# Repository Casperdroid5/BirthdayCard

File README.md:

A specialized birthdaycard containing personal text and jokes for my little brother. Containing word/component jokes on the silkscreen, 2 buttons to control the card and a few modes you can cycle trough. The code tells you everything you need. Feel free to redesign the card to your likings.

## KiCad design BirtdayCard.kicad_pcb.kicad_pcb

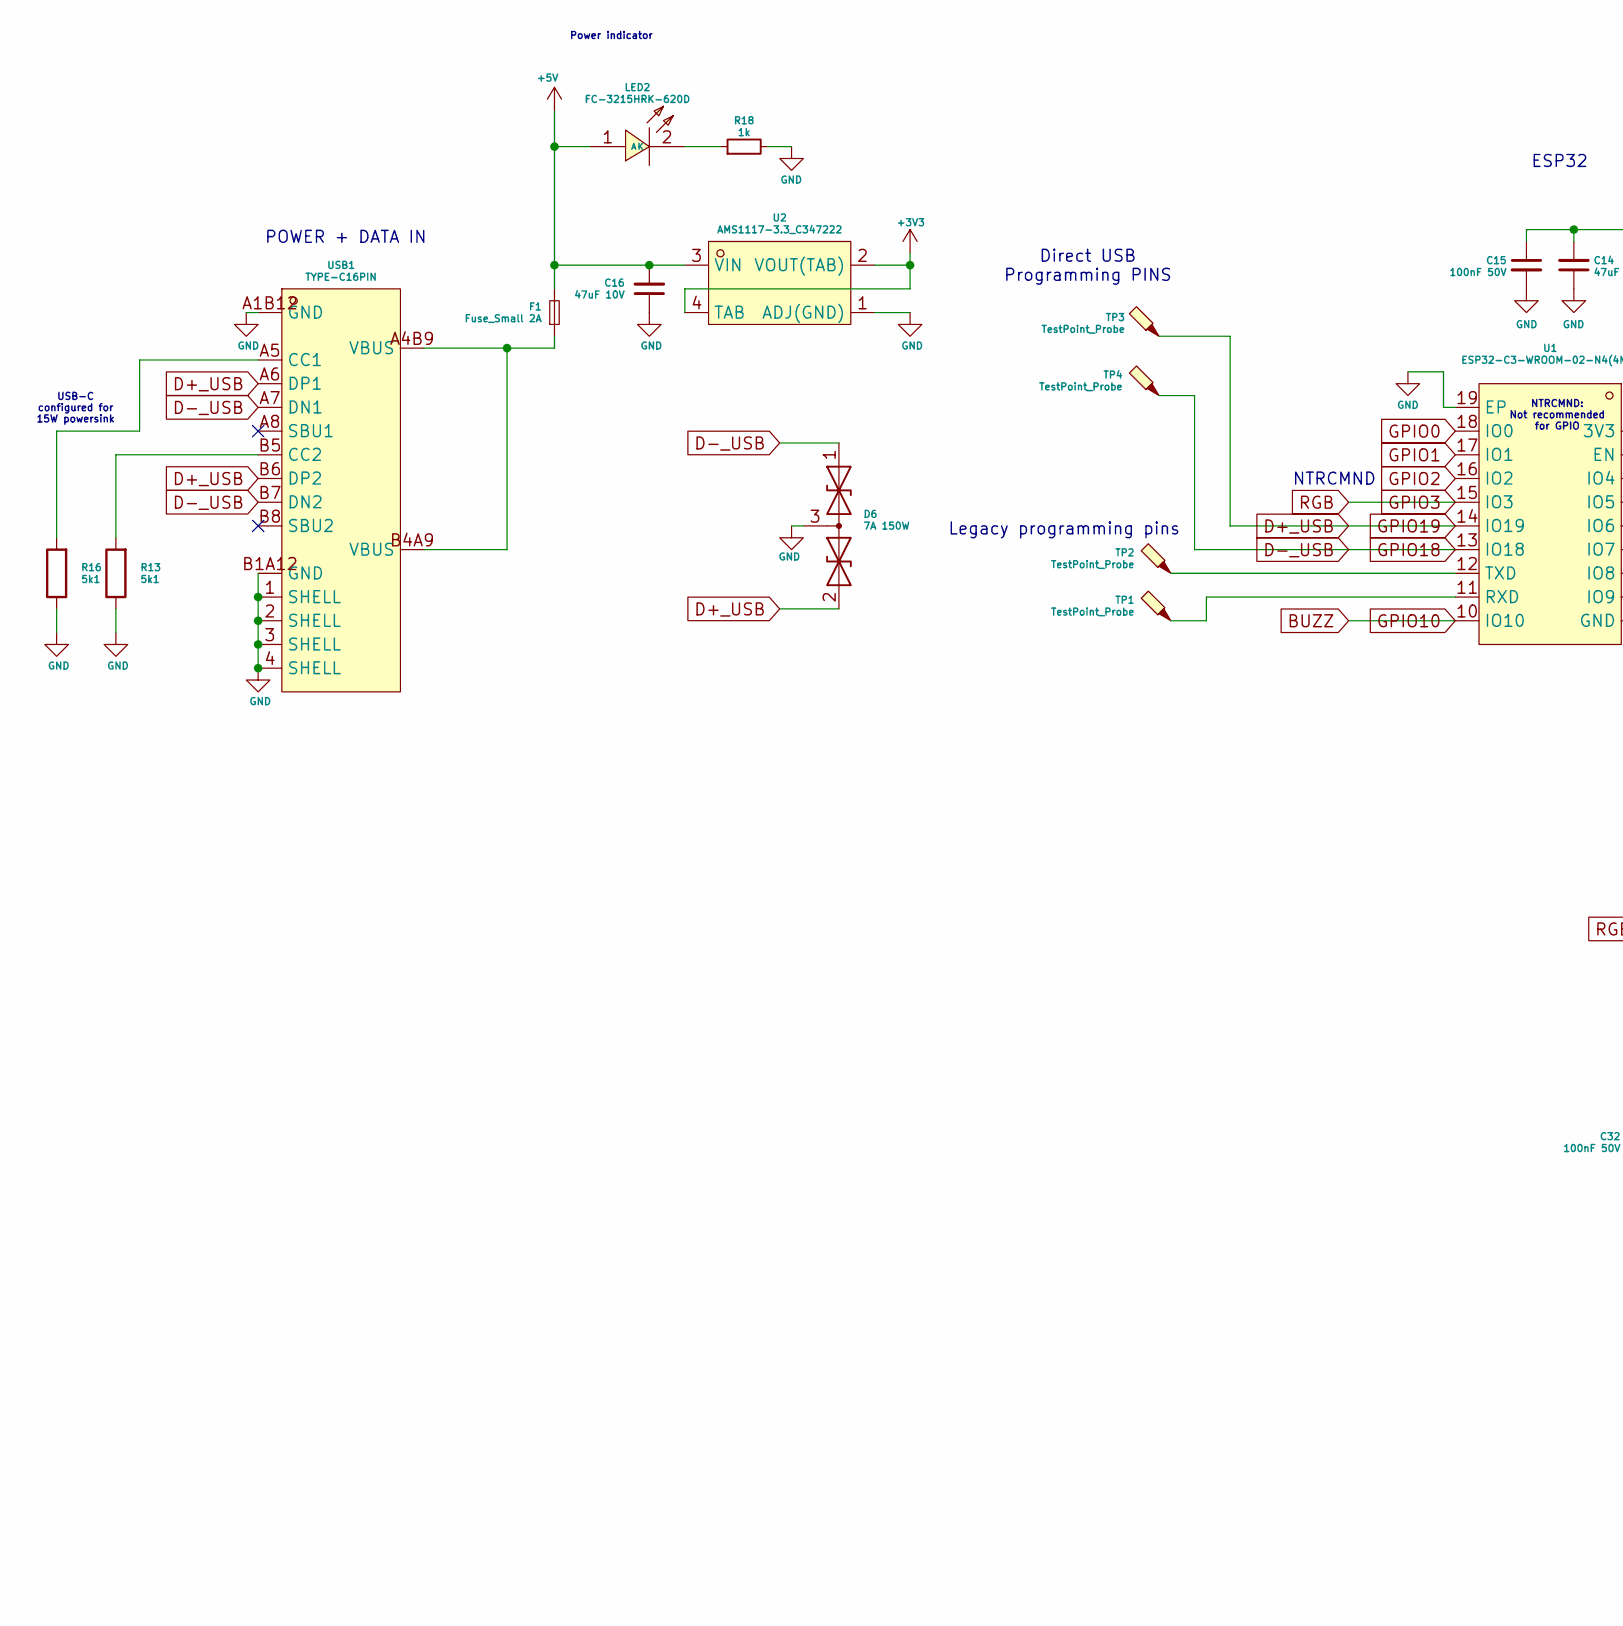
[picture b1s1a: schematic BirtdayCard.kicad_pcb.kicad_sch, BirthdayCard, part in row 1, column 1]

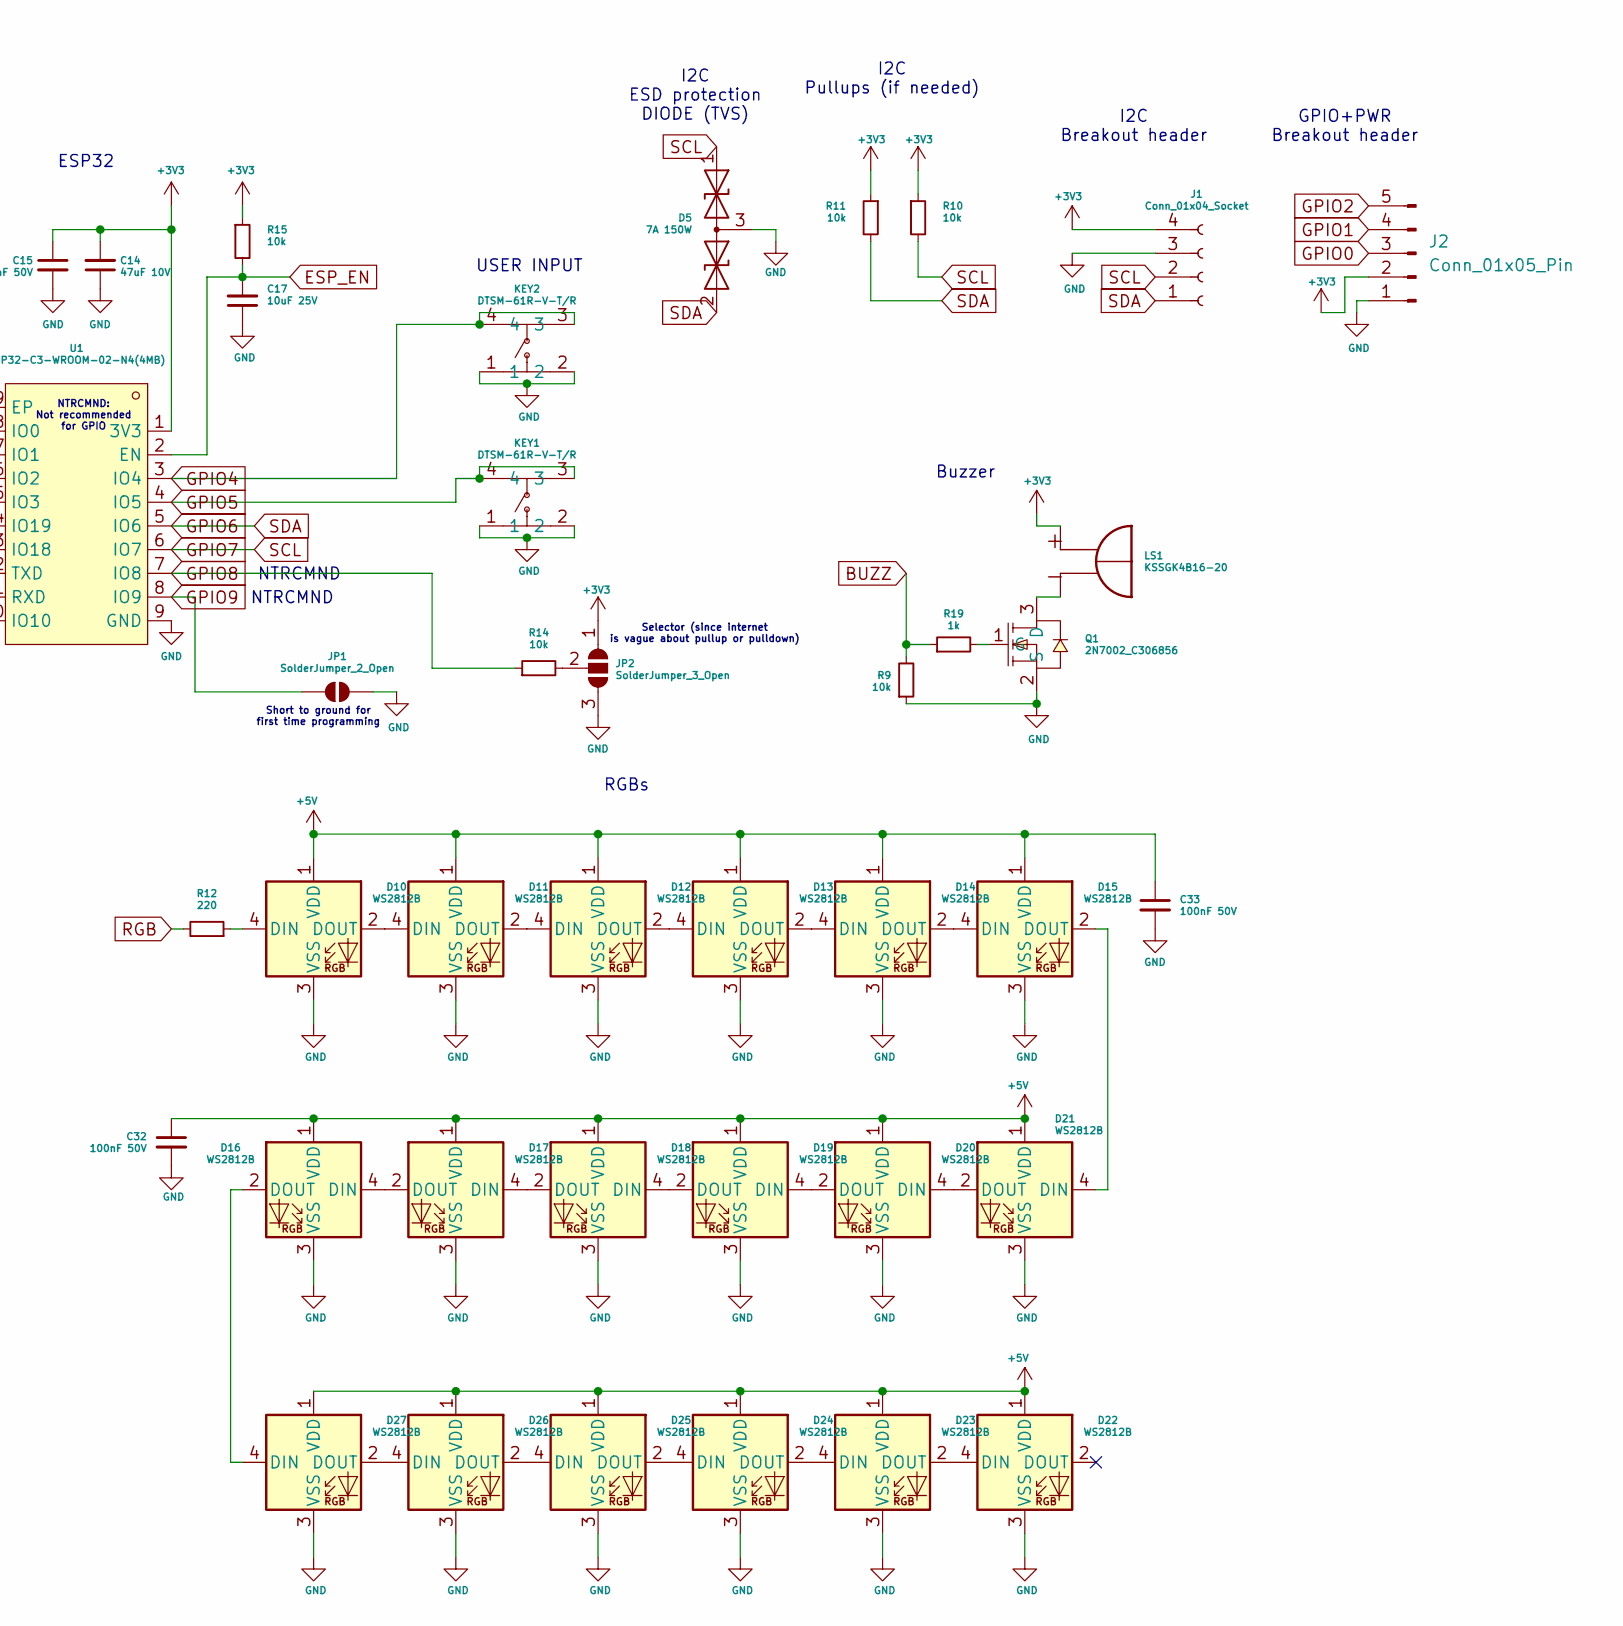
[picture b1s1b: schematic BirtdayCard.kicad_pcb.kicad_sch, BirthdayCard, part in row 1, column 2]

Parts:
C14, C16: 47uF 10V; C_1210_3225Metric_Pad1.33x2.70mm_HandSolder
C15, C32, C33: 100nF 50V; C_1210_3225Metric_Pad1.33x2.70mm_HandSolder
C17: 10uF 25V; C_1210_3225Metric_Pad1.33x2.70mm_HandSolder
D5, D6: 7A 150W; SOT-23_Handsoldering
D10, D11, D12, D13, D14, D15, D16, D17, D18, D19, D20, D21, D22, D23, D24, D25, D26, D27: WS2812B; LED-SMD_4P-L5.0-W5.0-BL_TC5050RGB
F1: Fuse_Small 2A; Fuse_1206_3216Metric_Pad1.42x1.75mm_HandSolder
J1: Conn_01x04_Socket; PinSocket_1x04_P2.54mm_Vertical
J2: Conn_01x05_Pin
JP1: SolderJumper_2_Open; SolderJumper-2_P1.3mm_Open_Pad1.0x1.5mm
JP2: SolderJumper_3_Open; SolderJumper-3_P1.3mm_Open_RoundedPad1.0x1.5mm
KEY1, KEY2: DTSM-61R-V-T/R; KEY-SMD_4P-L6.2-W6.2-P4.50-LS9.0; LCSC Part C224977
LED2: FC-3215HRK-620D; LED1206-R-RD_RED
LS1: KSSGK4B16-20; Buzzer KSSGK4B16-20; PARTREV 1.1
Q1: 2N7002_C306856; SOT-23-3_L2.9-W1.3-P1.90-LS2.4-BR
R9, R10, R11, R14, R15: 10k; R_1206_3216Metric_Pad1.30x1.75mm_HandSolder
R12: 220; R_1206_3216Metric_Pad1.30x1.75mm_HandSolder
R13, R16: 5k1; R_1206_3216Metric_Pad1.30x1.75mm_HandSolder
R18, R19: 1k; R_1206_3216Metric_Pad1.30x1.75mm_HandSolder
TP1, TP2, TP3, TP4: TestPoint_Probe; TestPoint_Pad_D2.0mm
U1: ESP32-C3-WROOM-02-N4(4MB); BULETM-SMD_ESPRESSIF_ESP32-C3-WROOM-02-N4-4MB
U2: AMS1117-3.3_C347222; SOT-223-4_L6.5-W3.5-P2.30-LS7.0-BR
USB1: TYPE-C16PIN; USB-C-SMD_TYPE-C16PIN; LCSC Part C393939

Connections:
+3V3: C14.2, C15.1, J1.4, J2.2, JP2.1 (A), LS1.P, R10.1, R11.1, R15.1, U1.1 (3V3), U2.2 (VOUT(TAB)), U2.4 (TAB)
+5V: C16.2, C32.1, C33.1, D10.1 (VDD), D11.1 (VDD), D12.1 (VDD), D13.1 (VDD), D14.1 (VDD), D15.1 (VDD), D16.1 (VDD), D17.1 (VDD), D18.1 (VDD), D19.1 (VDD), D20.1 (VDD), D21.1 (VDD), D22.1 (VDD), D23.1 (VDD), D24.1 (VDD), D25.1 (VDD), D26.1 (VDD), D27.1 (VDD), F1.2, LED2.1 (A), U2.3 (VIN)
BUZZ: R9.2, R19.1, U1.10 (IO10)
D+_USB: D6.2 (A2), TP3.1, U1.14 (IO19), USB1.A6 (DP1), USB1.B6 (DP2)
D-_USB: D6.1 (A1), TP4.1, U1.13 (IO18), USB1.A7 (DN1), USB1.B7 (DN2)
ESP_EN: C17.2, R15.2, U1.2 (EN)
GND: C14.1, C15.2, C16.1, C17.1, C32.2, C33.2, D5.3 (common), D6.3 (common), D10.3 (VSS), D11.3 (VSS), D12.3 (VSS), D13.3 (VSS), D14.3 (VSS), D15.3 (VSS), D16.3 (VSS), D17.3 (VSS), D18.3 (VSS), D19.3 (VSS), D20.3 (VSS), D21.3 (VSS), D22.3 (VSS), D23.3 (VSS), D24.3 (VSS), D25.3 (VSS), D26.3 (VSS), D27.3 (VSS), J1.3, J2.1, JP1.1 (A), JP2.3 (B), KEY1.1, KEY1.2, KEY2.1, KEY2.2, Q1.2 (S), R9.1, R13.1, R16.1, R18.2, U1.9 (GND), U1.19 (EP), U2.1 (ADJ(GND)), USB1.1 (SHELL), USB1.2 (SHELL), USB1.3 (SHELL), USB1.4 (SHELL), USB1.A1B12 (GND), USB1.B1A12 (GND)
GPIO0: J2.3, U1.18 (IO0)
GPIO1: J2.4, U1.17 (IO1)
GPIO2: J2.5, U1.16 (IO2)
GPIO3: R12.2, U1.15 (IO3)
GPIO4: KEY2.3, KEY2.4, U1.3 (IO4)
GPIO5: KEY1.3, KEY1.4, U1.4 (IO5)
GPIO6: D5.2 (A2), J1.1, R11.2, U1.5 (IO6)
GPIO7: D5.1 (A1), J1.2, R10.2, U1.6 (IO7)
GPIO8: R14.1, U1.7 (IO8)
GPIO9: JP1.2 (B), U1.8 (IO9)
unnamed: D10.4 (DIN), R12.1
unnamed: D10.2 (DOUT), D11.4 (DIN)
unnamed: D11.2 (DOUT), D12.4 (DIN)
unnamed: D12.2 (DOUT), D13.4 (DIN)
unnamed: D13.2 (DOUT), D14.4 (DIN)
unnamed: D14.2 (DOUT), D15.4 (DIN)
unnamed: D15.2 (DOUT), D21.4 (DIN)
unnamed: D16.4 (DIN), D17.2 (DOUT)
unnamed: D16.2 (DOUT), D27.4 (DIN)
unnamed: D17.4 (DIN), D18.2 (DOUT)
unnamed: D18.4 (DIN), D19.2 (DOUT)
unnamed: D19.4 (DIN), D20.2 (DOUT)
unnamed: D20.4 (DIN), D21.2 (DOUT)
unnamed: D22.4 (DIN), D23.2 (DOUT)
unnamed: D23.4 (DIN), D24.2 (DOUT)
unnamed: D24.4 (DIN), D25.2 (DOUT)
unnamed: D25.4 (DIN), D26.2 (DOUT)
unnamed: D26.4 (DIN), D27.2 (DOUT)
unnamed: F1.1, USB1.A4B9 (VBUS), USB1.B4A9 (VBUS)
unnamed: JP2.2 (C), R14.2
unnamed: LED2.2 (K), R18.1
unnamed: LS1.N, Q1.3 (D)
unnamed: Q1.1 (G), R19.2
unnamed: TP1.1, U1.11 (RXD)
unnamed: TP2.1, U1.12 (TXD)
unnamed: R16.2, USB1.A5 (CC1)
unnamed: R13.2, USB1.B5 (CC2)

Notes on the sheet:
NTRCMND
USER INPUT
NTRCMND: Not recommended for GPIO
GPIO+PWR Breakout header
USB-C configured for 15W powersink
Power indicator
RGBs
Direct USB Programming PINS
Selector (since internet is vague about pullup or pulldown)
Short to ground for first time programming
I2C Pullups (if needed)
Legacy programming pins
ESP32
I2C Breakout header
Buzzer
I2C ESD protection DIODE (TVS)
POWER + DATA IN

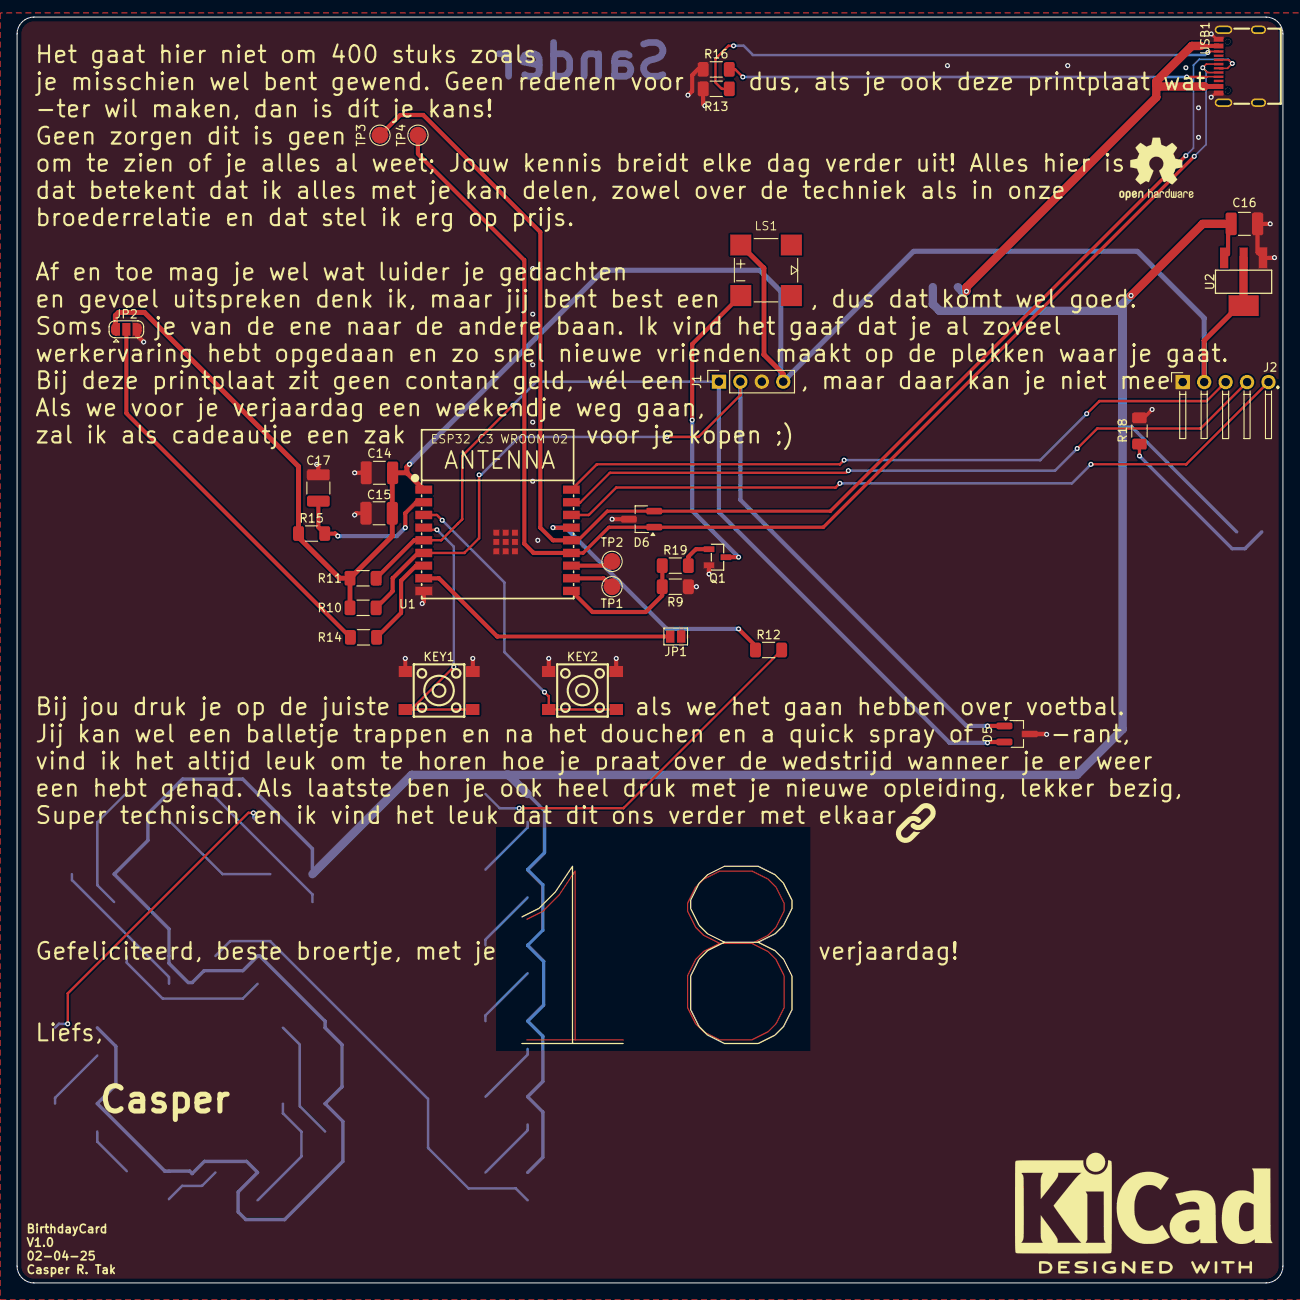
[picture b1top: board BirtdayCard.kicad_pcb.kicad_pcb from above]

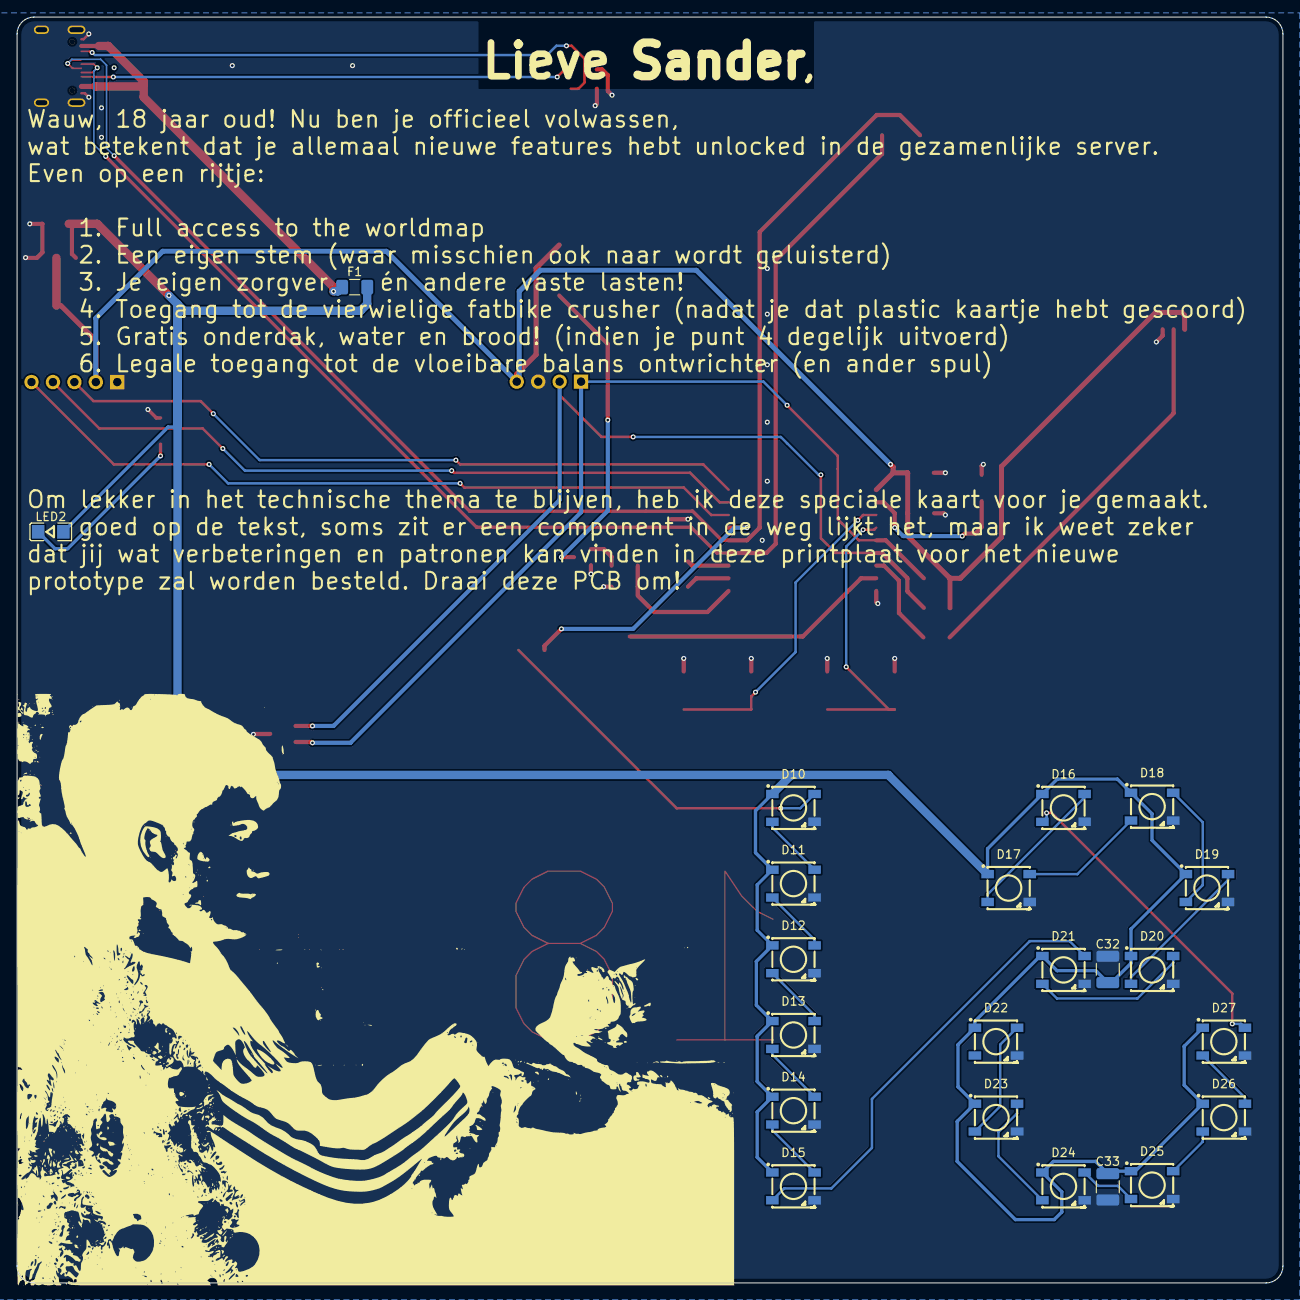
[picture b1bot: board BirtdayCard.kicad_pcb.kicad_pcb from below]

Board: 2 copper layers, 150.0 x 150.0 mm, 53 parts (22 on the bottom side), 44 nets.

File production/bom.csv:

Designator,Footprint,Quantity,Value,LCSC Part #
"C14, C16",1210,2,47uF 10V,
"C15, C32, C33",1210,3,100nF 50V,
C17,1210,1,10uF 25V,
"D10, D11, D12, D13, D14, D15, D16, D17, D18, D19, D20, D21, D22, D23, D24, D25, D26, D27",LED-SMD_4P-L5.0-W5.0-BL_TC5050RGB,18,WS2812B,
"D5, D6",SOT-23_Handsoldering,2,7A 150W,
F1,1206,1,Fuse_Small 2A,
J1,PinSocket_1x04_P2.54mm_Vertical,1,Conn_01x04_Socket,
J2,PinSocket_1x05_P2.54mm_Horizontal,1,Conn_01x05_Pin,
"KEY1, KEY2",KEY-SMD_4P-L6.2-W6.2-P4.50-LS9.0,2,DTSM-61R-V-T/R,C224977
LED2,LED1206-R-RD_RED,1,FC-3215HRK-620D,
LS1,Buzzer KSSGK4B16-20,1,KSSGK4B16-20,
Q1,SOT-23-3_L2.9-W1.3-P1.90-LS2.4-BR,1,2N7002_C306856,
"R10, R11, R14, R15, R9",1206,5,10k,
R12,1206,1,220,
"R13, R16",1206,2,5k1,
"R18, R19",1206,2,1k,
"TP1, TP2, TP3, TP4",TestPoint_Pad_D2.0mm,4,TestPoint_Probe,
U1,BULETM-SMD_ESPRESSIF_ESP32-C3-WROOM-02-N4-4MB,1,ESP32-C3-WROOM-02-N4(4MB),
U2,SOT-223-4_L6.5-W3.5-P2.30-LS7.0-BR,1,AMS1117-3.3_C347222,
USB1,USB-C-SMD_TYPE-C16PIN,1,TYPE-C16PIN,C393939

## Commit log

2025-03-29 Init
2025-03-29 Pin configurations ESP32
2025-03-30 adding components and consolidating with current parts
2025-03-30 USB configured and added LDO
2025-03-31 General layout improvements, added ESD protection and more LEDS
2025-03-31 archived 3D models
2025-04-01 added buzzer components and pwr LED
2025-04-01 Finished V1 of schematic
2025-04-01 Starting PCB design
2025-04-01 Enlarged PCB and working on text
2025-04-01 Concept 1 PCB
2025-04-02 board improvements and added media
2025-04-02 Improved silkscreen and text
2025-04-02 Updated schematic and PCB (resistor removed)
2025-04-02 updated text
2025-04-02 Finished PCB, ordered model
2025-04-02 changed date
2025-04-03 Cleanup
2025-04-03 PCB screenshots
2025-04-04 updated PDF
2025-04-11 Code for card
2025-04-11 18 led followup now correct in software
2025-04-11 settings improved
2025-04-11 Confetti mode!
2025-04-11 improved brightness code
2025-04-11 added webpage to secret confetti mode
2025-04-11 Minor webpage improvements
2025-04-11 Updated sch and pdf
2025-04-22 updated code hieperdepiep and confetti mode
2025-04-22 added special fading modes next to the standard static coulours.
